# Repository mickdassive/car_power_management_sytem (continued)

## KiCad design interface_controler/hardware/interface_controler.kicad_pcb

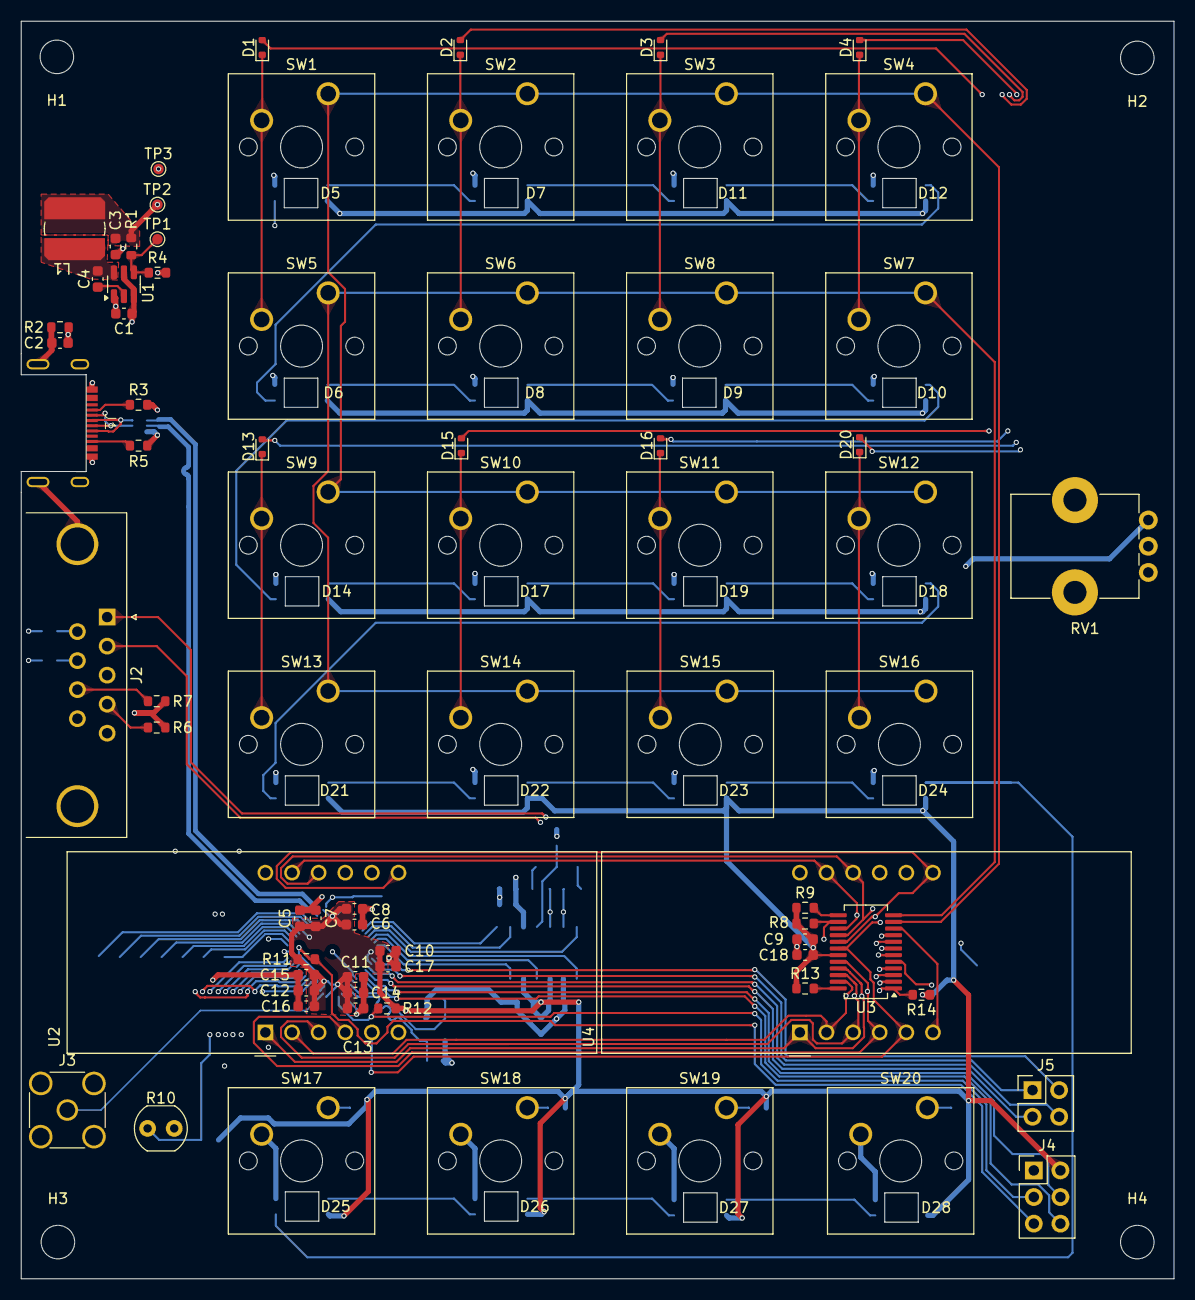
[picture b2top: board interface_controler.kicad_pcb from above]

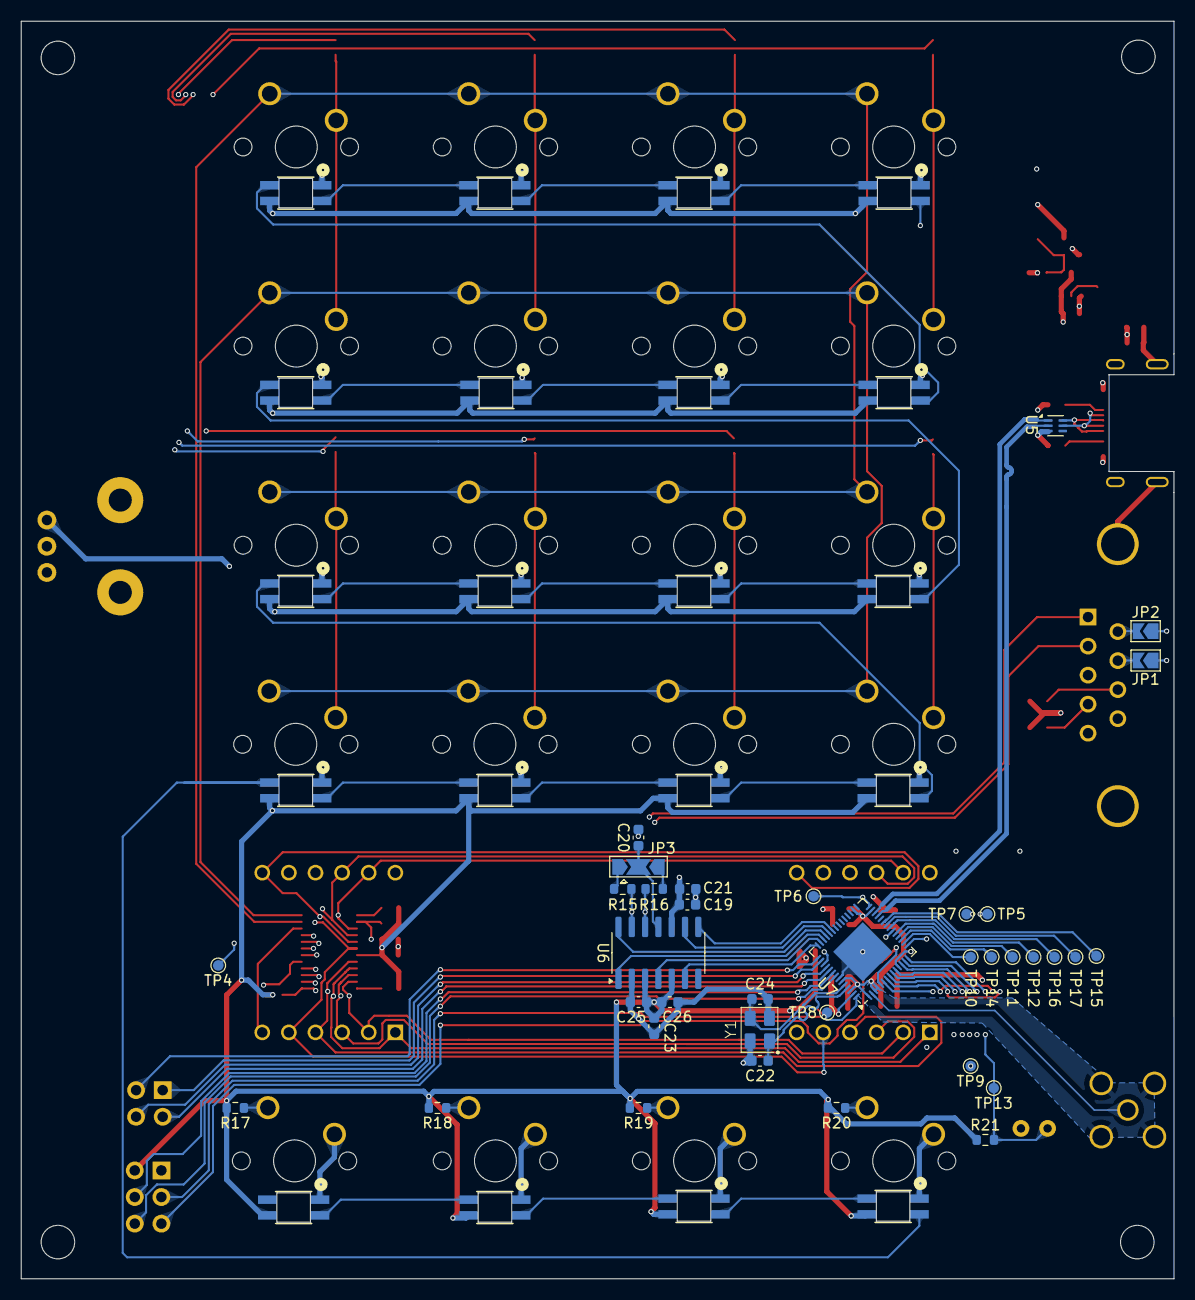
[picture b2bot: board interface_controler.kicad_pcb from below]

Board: 4 copper layers, 110.0 x 120.0 mm, 134 parts (36 on the bottom side), 104 nets.

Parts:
C1, C6, C7, C9, C10, C11, C13, C15, C19, C23: 10uF; C_0603_1608Metric
C2, C4, C5, C8, C12, C14, C16, C17, C20, C21, C25, C26: 0uF1; C_0603_1608Metric
C3: 22uF; C_0603_1608Metric
C18: 0.1uF; C_0603_1608Metric
C22, C24: 8pF2; C_0603_1608Metric
D1, D2, D3, D4, D13, D15, D16, D20: 1N4448X-TP; D_SOD-523
D5, D6, D7, D8, D9, D10, D11, D12, D14, D17, D18, D19, D21, D22, D23, D24, D25, D26, D27, D28: K6812-E; 4960_ADA
H1, H2, H3, H4: MountingHole; MountingHole_3.2mm_M3
J1: usb4500
J2: DSUB-9_Pins_Horizontal_P2.77x2.84mm_EdgePinOffset4.94mm_Hou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
J3: Conn_Coaxial; SMA_Amphenol_132291-12_Vertical
J4: PROG_PORT; PinHeader_2x03_P2.54mm_Vertical
J5: JTAG; PinHeader_2x02_P2.54mm_Vertical
JP1, JP2: SolderJumper-2_P1.3mm_Open_TrianglePad1.0x1.5mm
JP3: SolderJumper-3_P2.0mm_Open_TrianglePad1.0x1.5mm
L1: 3uH3; L_Bourns_SDR0604
R1: 31K6; R_0603_1608Metric
R2: 330R; R_0603_1608Metric
R3, R5: 5K1; R_0603_1608Metric
R4, R6, R7, R9, R11, R12, R13, R17, R18, R19, R20: 10K; R_0603_1608Metric
R8, R14: 2K2; R_0603_1608Metric
R10: PDV-P9203; R_LDR_4.9x4.2mm_P2.54mm_Vertical
R15, R16: 60R4; R_0603_1608Metric
R21: 22K; R_0603_1608Metric
RV1: 10K; Potentiometer_Bourns_PTV09A-1_Single_Vertical
SW1: CH_1; SW_Cherry_MX_1.00u_PCB
SW2: CH_2; SW_Cherry_MX_1.00u_PCB
SW3: CH_3; SW_Cherry_MX_1.00u_PCB
SW4: CH_4; SW_Cherry_MX_1.00u_PCB
SW5: CH_5; SW_Cherry_MX_1.00u_PCB
SW6: CH_6; SW_Cherry_MX_1.00u_PCB
SW7: CH_8; SW_Cherry_MX_1.00u_PCB
SW8: CH_7; SW_Cherry_MX_1.00u_PCB
SW9: CH_9; SW_Cherry_MX_1.00u_PCB
SW10: CH_10; SW_Cherry_MX_1.00u_PCB
SW11: CH_11; SW_Cherry_MX_1.00u_PCB
SW12: CH_12; SW_Cherry_MX_1.00u_PCB
SW13: CH_13; SW_Cherry_MX_1.00u_PCB
SW14: CH_14; SW_Cherry_MX_1.00u_PCB
SW15: CH_15; SW_Cherry_MX_1.00u_PCB
SW16: CH_16; SW_Cherry_MX_1.00u_PCB
SW17: USER_ENTER; SW_Cherry_MX_1.00u_PCB
SW18: USER_UP; SW_Cherry_MX_1.00u_PCB
SW19: USER_DOWN; SW_Cherry_MX_1.00u_PCB
SW20: USER_BACK; SW_Cherry_MX_1.00u_PCB
TP1, TP2, TP3, TP4, TP5, TP6, TP7, TP8, TP9, TP10, TP11, TP12, TP13, TP14, TP15, TP16, TP17: TestPoint_Pad_D1.0mm
U1: AP62150WU; TSOT-23-6
U2, U4: LTC-5723HR; CA56-12CGKWA
U3: AS1115-BSST; QSOP-24_3.9x8.7mm_P0.635mm
U5: ECMF02-2AMX6; ST_UQFN-6L_1.5x1.7mm_P0.5mm
U6: TJA1043T/1J; SOIC-14_3.9x8.7mm_P1.27mm
U7: ESP32-S2FH2; QFN-56-1EP_7x7mm_P0.4mm_EP4x4mm
Y1: 40 MHz; cx3225sa_e

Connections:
+3V3: C3.1, C5.1, C6.1, C7.1, C8.1, C9.1, C10.1, C11.1, C12.1, C13.1, C14.1, C15.1, C16.1, C17.1, C18.1, C23.1, C25.1, C26.1, D5.3 (VDD), D6.3 (VDD), D7.3 (VDD), D8.3 (VDD), D9.3 (VDD), D10.3 (VDD), D11.3 (VDD), D12.3 (VDD), D14.3 (VDD), D17.3 (VDD), D18.3 (VDD), D19.3 (VDD), D21.3 (VDD), D22.3 (VDD), D23.3 (VDD), D24.3 (VDD), D25.3 (VDD), D26.3 (VDD), D27.3 (VDD), D28.3 (VDD), J4.2, L1.2, R1.1, R6.2, R7.2, R8.1, R9.1, R11.1, R12.1, R13.1, R14.1, R17.2, R18.2, R19.2, R20.2, R21.1, RV1.1, TP2.1, U3.19 (VDD), U6.3 (VCC), U6.5 (VIO), U7.1 (VDDA), U7.3 (VDD3P3), U7.4 (VDD3P3), U7.20 (VDD3P3_RTC), U7.27 (VDD3P3_RTC_IO), U7.30 (VDD_SPI), U7.45 (VDD3P3_CPU), U7.51 (VDDA), U7.54 (VDDA)
+12V: C1.1, C19.1, C21.1, J2.3, U1.3 (VIN), U1.5 (EN), U6.10 (VBAT)
BLACKOUT: J2.8, R7.1
CAN_EN: U6.6 (EN), U7.42 (GPIO38)
CAN_ERR: U6.8 (~ERR), U7.37 (GPIO33)
CAN_H: J2.1, R15.1, U6.13 (CANH)
CAN_L: J2.2, R16.2, U6.12 (CANL)
CAN_RX: U6.4 (RXD), U7.41 (GPIO37)
CAN_STB: U6.14 (~STB), U7.39 (GPIO35)
CAN_TX: U6.1 (TXD), U7.40 (GPIO36)
CAN_WAKE: U6.9 (WAKE), U7.38 (GPIO34)
DISP_DIG_0: U2.12 (CC1), U3.2 (DIG0)
DISP_DIG_1: U2.9 (CC2), U3.3 (DIG1)
DISP_DIG_2: U2.8 (CC3), U3.4 (DIG2)
DISP_DIG_3: U2.6 (CC4), U3.5 (DIG3)
DISP_DIG_4: U3.7 (DIG4), U4.12 (CC1)
DISP_DIG_5: U3.8 (DIG5), U4.9 (CC2)
DISP_DIG_6: U3.9 (DIG6), U4.8 (CC3)
DISP_DIG_7: U3.10 (DIG7), U4.6 (CC4)
DISP_IRQ: R13.2, U3.24 (IRQ)
DISP_KEY_A: SW1.1, SW2.1, SW3.1, SW4.1, SW9.1, SW10.1, SW11.1, SW12.1, U3.11 (KEYA)
DISP_KEY_B: SW5.1, SW6.1, SW7.1, SW8.1, SW13.1, SW14.1, SW15.1, SW16.1, U3.12 (KEYB)
DISP_SEG_A: D1.2 (A), U2.11 (a), U3.15 (SEGA), U4.11 (a)
DISP_SEG_B: D2.2 (A), U2.7 (b), U3.17 (SEGB), U4.7 (b)
DISP_SEG_C: D3.2 (A), U2.4 (c), U3.20 (SEGC), U4.4 (c)
DISP_SEG_D: D4.2 (A), U2.2 (d), U3.23 (SEGD), U4.2 (d)
DISP_SEG_DP: D20.2 (A), U2.3 (DPX), U3.22 (SEGDP), U4.3 (DPX)
DISP_SEG_E: D13.2 (A), U2.1 (e), U3.21 (SEGE), U4.1 (e)
DISP_SEG_F: D15.2 (A), U2.10 (f), U3.16 (SEGF), U4.10 (f)
DISP_SEG_G: D16.2 (A), U2.5 (g), U3.18 (SEGG), U4.5 (g)
ESP_IO0: J4.5, R11.2, U7.5 (GPIO0)
ESP_RX: J4.6, U7.49 (U0RXD)
ESP_TX: J4.4, U7.48 (U0TXD)
GND: C1.2, C2.2, C3.2, C5.2, C6.2, C7.2, C8.2, C9.2, C10.2, C11.2, C12.2, C13.2, C14.2, C15.2, C16.2, C17.2, C18.2, C19.2, C20.2, C21.2, C22.2, C23.2, C24.2, C25.2, C26.2, D5.1 (VSS), D6.1 (VSS), D7.1 (VSS), D8.1 (VSS), D9.1 (VSS), D10.1 (VSS), D11.1 (VSS), D12.1 (VSS), D14.1 (VSS), D17.1 (VSS), D18.1 (VSS), D19.1 (VSS), D21.1 (VSS), D22.1 (VSS), D23.1 (VSS), D24.1 (VSS), D25.1 (VSS), D26.1 (VSS), D27.1 (VSS), D28.1 (VSS), J1.A1 (GND), J1.B1 (GND), J2.5, J3.2 (Ext), J4.1, R2.2, R3.2, R4.2, R5.2, R10.2, RV1.3, SW17.2, SW18.2, SW19.2, SW20.2, TP3.1, U1.1 (GND), U3.6 (GND), U5.3 (GND), U6.2 (GND), U7.50 (GPIO45), U7.55 (GPIO46), U7.57 (GND), Y1.2, Y1.4
GNDS: C2.1, J1.S (SHIELD), J2.0 (PAD), R2.1
I2C_SCL: JP2.1 (A), R8.2, TP7.1, U3.14 (SCL), U7.7 (GPIO2)
I2C_SDA: JP1.1 (A), R14.2, TP5.1, U3.1 (SDA), U7.8 (GPIO3)
KB_NEOPIXELS: D5.2 (DIN), U7.15 (GPIO10)
LIGHT_ADJUST: RV1.2, TP4.1, U7.11 (GPIO6)
LIGHT_SENSE: R10.1, R21.2, TP13.1, U7.14 (GPIO9)
LNA: J3.1 (In), U7.2 (LNA_IN)
MTCK: J5.2, U7.43 (MTCK)
MTD0: J5.1, U7.44 (MTD0)
MTDI: J5.4, U7.46 (MDTI)
MTMS: J5.3, U7.47 (MTMS)
unnamed: D1.1 (K), SW1.2, SW5.2
unnamed: D2.1 (K), SW2.2, SW6.2
unnamed: D3.1 (K), SW3.2, SW8.2
unnamed: D4.1 (K), SW4.2, SW7.2
unnamed: D20.1 (K), SW12.2, SW16.2
unnamed: D16.1 (K), SW11.2, SW15.2
unnamed: D15.1 (K), SW10.2, SW14.2
unnamed: D13.1 (K), SW9.2, SW13.2
unnamed: D5.4 (DOUT), D7.2 (DIN)
unnamed: D7.4 (DOUT), D11.2 (DIN)
unnamed: D11.4 (DOUT), D12.2 (DIN)
unnamed: D6.2 (DIN), D12.4 (DOUT)
unnamed: D6.4 (DOUT), D8.2 (DIN)
unnamed: D8.4 (DOUT), D9.2 (DIN)
unnamed: D9.4 (DOUT), D10.2 (DIN)
unnamed: D10.4 (DOUT), D14.2 (DIN)
unnamed: D14.4 (DOUT), D17.2 (DIN)
unnamed: D17.4 (DOUT), D19.2 (DIN)
unnamed: D18.2 (DIN), D19.4 (DOUT)
unnamed: D18.4 (DOUT), D21.2 (DIN)
unnamed: D21.4 (DOUT), D22.2 (DIN)
unnamed: D22.4 (DOUT), D23.2 (DIN)
unnamed: D23.4 (DOUT), D24.2 (DIN)
unnamed: D24.4 (DOUT), D25.2 (DIN)
unnamed: D25.4 (DOUT), D26.2 (DIN)
unnamed: D26.4 (DOUT), D27.2 (DIN)
unnamed: D27.4 (DOUT), D28.2 (DIN)
unnamed: J1.A5 (CC1), R3.1
unnamed: J1.B5 (CC2), R5.1
unnamed: JP3.1 (A), R15.2
unnamed: JP3.3 (B), R16.1
unnamed: C20.1, JP3.2 (C), U6.11 (SPLIT)
unnamed: J2.6, JP2.2 (B)
unnamed: J2.7, JP1.2 (B)
unnamed: TP15.1, U7.23 (DAC_1)
unnamed: TP9.1, U7.6 (GPIO1)
unnamed: TP10.1, U7.16 (GPIO11)
unnamed: TP14.1, U7.17 (GPIO12)
unnamed: TP11.1, U7.18 (GPIO13)
unnamed: TP12.1, U7.19 (GPIO14)
unnamed: TP6.1, U7.28 (GPIO21)
unnamed: TP17.1, U7.22 (XTAL_32K_N)
unnamed: TP16.1, U7.21 (XTAL_32K_P)
unnamed: C24.1, U7.52 (XTAL_N), Y1.3
unnamed: C22.1, U7.53 (XTAL_P), Y1.1
unnamed: R9.2, U3.13 (ISET)
unnamed: C4.2, L1.1, U1.6 (BST)
unnamed: R1.2, R4.1, TP1.1, U1.4 (FB)
unnamed: C4.1, U1.2 (SW)
OFF_ROAD: J2.4, R6.1
RST: J4.3, R12.2, TP8.1, U7.56 (CHIP_PU)
USB_C_N: J1.A7 (D-), J1.B7 (D-), U5.5 (D-_out)
USB_C_P: J1.A6 (D+), J1.B6 (D+), U5.6 (D+_out)
USB_N: U5.2 (D-_in), U7.25 (GPIO19/USB_D-)
USB_P: U5.1 (D+_in), U7.26 (GPIO20/USB_D+)
USER_BACK: R17.1, SW20.1, U7.9 (GPIO4)
USER_DOWN: R18.1, SW19.1, U7.10 (GPIO5)
USER_ENTER: R20.1, SW17.1, U7.13 (GPIO8)
USER_UP: R19.1, SW18.1, U7.12 (GPIO7)

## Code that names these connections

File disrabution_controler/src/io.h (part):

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  int io_chanel_number;
  in_out pin_mode;       //defines pinmode see enum above for deatails
  bool* is_faulted; //if true, pin is in fault state
  bool blackout; //if true, pin shold be disabled in blackout mode
  bool is_ofroad; //if true, pin shold only be used in off-road mode
  bool onboard;          //If true, IO is on ESP8266; if false, IO is on IO expander
  void (*interrupt_handler)(struct pin); // Pointer to interrupt handler function (optional)
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
};
//BE SURE TO ADD PINS TO BOTH THE "pin" STRUCT AND THE "pin_names" ARRAY THEY MUST MATCH
//io_call struct defines  {mask, port, pin, pin_mo if blackout ise, onboard, interrupt_handler(optional)}
static struct pin sda {0x00, 2, 2, -1, -1, -1, i2c, nullptr, false, false, true};
static struct pin scl {0x00, 3, 3, -1, -1, -1, i2c, nullptr, false, false, true};
static struct pin iox_0_int {0x00, -1, 1, -1, -1, -1, intr, nullptr, false, false, false};
static struct pin car_acc {0x00, -1, 4, -1, -1, -1, in, nullptr, false, false, true};
static struct pin peripheral_pwr_gate {0x00, -1, 5, -1, -1, 17, out, &ch17_faulted, false, false, true};
static struct pin gpio_6 {0x00, -1, 6, -1, -1, -1, in, nullptr, false, false, true};
static struct pin gpio_7 {0x00, -1, 7, -1, -1, -1, in, nullptr, false, false, true};
static struct pin gpio_8 {0x00, -1, 8, -1, -1, -1, in, nullptr, false, false, true};
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static struct pin gpio_10 {0x00, -1, 10, -1, -1, -1, in, nullptr, false, false, true};
static struct pin gpio_11 {0x00, -1, 11, -1, -1, -1, in, nullptr, false, false, true};
static struct pin gpio_12 {0x00, -1, 12, -1, -1, -1, in, nullptr, false, false, true};
static struct pin peripheral_pwr_csn {0x00, -1, 13, -1, -1, 17, analog_in, &ch17_faulted, false, false, true, nullptr, &peripheral_current_limit};
static struct pin ref_12v {0x00, -1, 14, -1, -1, 0, analog_in, nullptr, false, false, true};
static struct pin dac_1 {0x00, -1, 15, -1, -1, -1, analog_out, nullptr, false, false, true};
static struct pin dac_2 {0x00, -1, 16, -1, -1, -1, analog_out, nullptr, false, false, true};
static struct pin usb_d_n {0x00, -1, 19, -1, -1, -1, usb, nullptr, false, false, true};
static struct pin usb_d_p {0x00, -1, 20, -1, -1, -1, usb, nullptr, false, false, true};
static struct pin disrabution_neo_pixels {0x00, -1, 21, -1, -1, -1, out, nullptr, false, false, true};
static struct pin adc_1_alert {0x00, -1, 15, 1, -1, -1, intr, nullptr, false, false, true, adc_alert_handler};
static struct pin adc_2_alert {0x00, -1, 16, 2, -1, -1, intr, nullptr, false, false, true, adc_alert_handler};
static struct pin can_err {0x00, -1, 33, -1, -1, -1, in, nullptr, false, false, true};
static struct pin can_wake {0x00,-1, 34, -1, -1, -1, intr, nullptr, false, false, true};
static struct pin can_stb {0x00, -1, 35, -1, -1, -1, out, nullptr, false, false, true};
static struct pin can_tx {0x00, -1, 36, -1, -1, -1, out, nullptr, false, false, true};
static struct pin can_en {0x00, -1, 38, -1, -1, -1, out, nullptr, false, false, true};
static struct pin can_rx {0x00, -1, 37, -1, -1, -1, in, nullptr, false, false, true};
static struct pin ch1_gate {0x80, 0, 11, 1, 0, 1, out, &ch1_faulted, false, false, false};
static struct pin ch2_gate {0x40, 0, 10, 1, 1, 2, out, &ch2_faulted, false, false, false};
static struct pin ch3_gate {0x20, 0, 9, 1, 2, 3, out, &ch3_faulted, false, false, false};
static struct pin ch4_gate {0x10, 0, 8, 1, 3, 4, out, &ch4_faulted, false, false, false};
static struct pin ch5_gate {0x08, 0, 7, 1, 4, 5, out, &ch5_faulted, false, false, false};
static struct pin ch6_gate {0x04, 0, 6, 1, 5, 6, out, &ch6_faulted, false, false, false};
static struct pin ch7_gate {0x02, 0, 5, 1, 6, 7, out, &ch7_faulted, false, false, false};
static struct pin ch8_gate {0x01, 0, 4, 1, 7, 8, out, &ch8_faulted, false, false, false};
static struct pin ch9_gate {0x80, 1, 20, 2, 0, 9, out, &ch9_faulted, false, false, false};
static struct pin ch10_gate {0x40, 1, 19, 2, 1, 10, out, &ch10_faulted, false, false, false};
static struct pin ch11_gate {0x20, 1, 18, 2, 2, 11, out, &ch11_faulted, false, false, false};
static struct pin ch12_gate {0x10, 1, 17, 2, 3, 12, out, &ch12_faulted, false, false, false};
static struct pin ch13_gate {0x08, 1, 16, 2, 4, 13, out, &ch13_faulted, false, false, false};
static struct pin ch14_gate {0x04, 1, 15, 2, 5, 14, out, &ch14_faulted, false, false, false};
static struct pin ch15_gate {0x02, 1, 14, 2, 6, 15, out, &ch15_faulted, false, false, false};
static struct pin ch16_gate {0x01, 1, 13, 2, 7, 16, out, &ch16_faulted, false, false, false};
static struct pin ch1_csn {0x00, -1, 6, 1, 0, 1, analog_in, &ch1_faulted, false, false, false, nullptr, &ch1_current_limit};
static struct pin ch2_csn {0x00, -1, 5, 1, 1, 2, analog_in, &ch2_faulted, false, false, false, nullptr, &ch2_current_limit};
static struct pin ch3_csn {0x00, -1, 4, 1, 2, 3, analog_in, &ch3_faulted, false, false, false, nullptr, &ch3_current_limit};
static struct pin ch4_csn {0x00, -1, 3, 1, 3, 4, analog_in, &ch4_faulted, false, false, false, nullptr, &ch4_current_limit};
static struct pin ch5_csn {0x00, -1, 2, 1, 4, 5, analog_in, &ch5_faulted, false, false, false, nullptr, &ch5_current_limit};
static struct pin ch6_csn {0x00, -1, 1, 1, 5, 6, analog_in, &ch6_faulted, false, false, false, nullptr, &ch6_current_limit};
static struct pin ch7_csn {0x00, -1, 16, 1, 6, 7, analog_in, &ch7_faulted, false, false, false, nullptr, &ch7_current_limit};
static struct pin ch8_csn {0x00, -1, 15, 1, 7, 8, analog_in, &ch8_faulted, false, false, false, nullptr, &ch8_current_limit};
static struct pin ch9_csn {0x00, -1, 6, 2, 0, 9, analog_in, &ch9_faulted, false, false, false, nullptr, &ch9_current_limit};
static struct pin ch10_csn {0x00, -1, 5, 2, 1, 10, analog_in, &ch10_faulted, false, false, false, nullptr, &ch10_current_limit};
static struct pin ch11_csn {0x00, -1, 4, 2, 2, 11, analog_in, &ch11_faulted, false, false, false, nullptr, &ch11_current_limit};
static struct pin ch12_csn {0x00, -1, 3, 2, 3, 12, analog_in, &ch12_faulted, false, false, false, nullptr, &ch12_current_limit};
static struct pin ch13_csn {0x00, -1, 2, 2, 4, 13, analog_in, &ch13_faulted,false, false, false, nullptr, &ch13_current_limit};
static struct pin ch14_csn {0x00, -1, 1, 2, 5, 14, analog_in, &ch14_faulted, false, false, false, nullptr, &ch14_current_limit};
static struct pin ch15_csn {0x00, -1, 16, 2, 6, 15, analog_in, &ch15_faulted, false, false, false, nullptr, &ch15_current_limit};
static struct pin ch16_csn {0x00, -1, 15, 2, 7, 16, analog_in, &ch16_faulted, false, false, false, nullptr, &ch16_current_limit};
static struct pin null_pin {0x00, -1, -1, -1, -1, -1, empty_pin, nullptr, false, false, false, nullptr, nullptr};

 
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
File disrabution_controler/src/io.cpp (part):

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QueueHandle_t channelStateQueue = xQueueCreate(1, sizeof(uint32_t));

//neopixel object
Adafruit_NeoPixel strip((uint16_t)io_num_pixels, (int)disrabution_neo_pixels.pin_number, NEO_GRB + NEO_KHZ800);


/**
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      if (pin_names[i]->pin_mode == i2c) {
        if (i2c_sda == -1) {
          if (pin_names[i]->port == 2) {
            i2c_sda = pin_names[i]->pin_number;
          }
        } else if (i2c_scl == -1) {
          if (pin_names[i]->port == 3) {
            i2c_scl = pin_names[i]->pin_number;
          }
        }
        
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 *
 * Dependencies:
 * - Requires Adafruit_NeoPixel library.
 * - Uses global variables: io_num_pixels, disrabution_neo_pixels.pin_number, pixel_type.
 *
 * @note This function should be called during system initialization before using the NeoPixel strip.
 */
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
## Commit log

2025-05-28 started work on hardware design for the disrabution controler
2025-05-29 more hardware work
2025-05-29 MORE PCB WORK
2025-05-30 more hardware work on disrabution controler nearing ifc
2025-06-06 completed interface controler hardware
2025-06-06 working on firmware but notaced a hardware issue
2025-06-06 fixed haredware issue
2025-06-06 working on adc drivers and starting task handleing
2025-06-06 updated r values
2025-06-06 debugging
2025-06-08 Remove submodule path/to/submodule
2025-06-08 added esp-idf submodule
2025-06-08 working on canbus
2025-06-09 working on canbus implimentation
2025-06-10 working on canbus coms
2025-06-19 reworkd some of the adc and can code
2025-06-19 remove unneed decleration
2025-06-20 reworked debug system
2025-06-20 debug fix
2025-07-08 changed programing headder
2025-07-08 fixed programing connector
